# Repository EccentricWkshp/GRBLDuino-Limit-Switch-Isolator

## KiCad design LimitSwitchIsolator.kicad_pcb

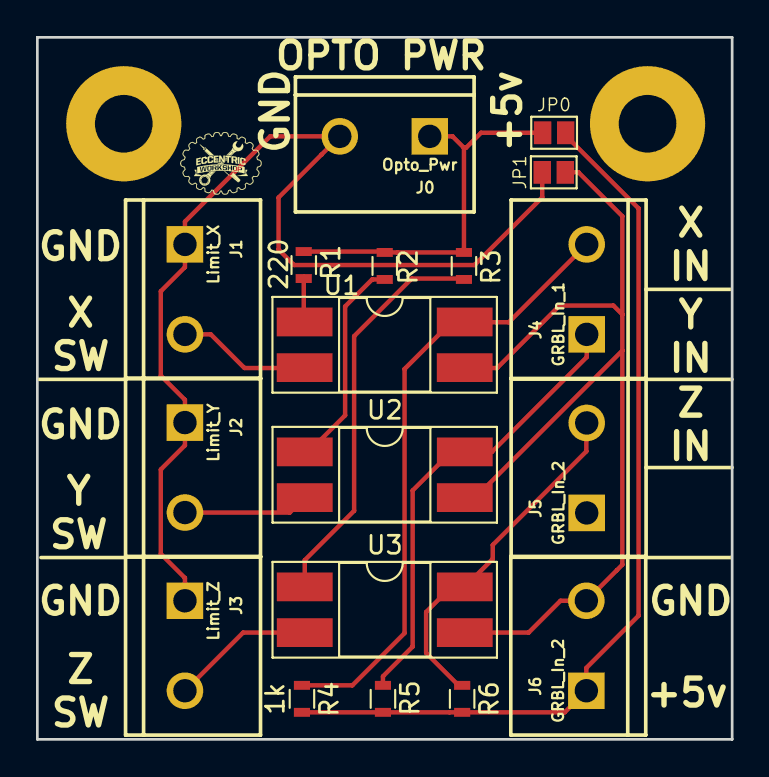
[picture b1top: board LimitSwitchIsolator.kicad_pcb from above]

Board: 2 copper layers, 38.6 x 39.0 mm, 18 parts (0 on the bottom side), 13 nets.

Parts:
J0: Opto_Pwr; SPARKFUN-CONNECTORS_SCREWTERMINAL-5MM-2
J1: Limit_X; SPARKFUN-CONNECTORS_SCREWTERMINAL-5MM-2
J2: Limit_Y; SPARKFUN-CONNECTORS_SCREWTERMINAL-5MM-2
J3: Limit_Z; SPARKFUN-CONNECTORS_SCREWTERMINAL-5MM-2
J4: GRBL_In_1; SPARKFUN-CONNECTORS_SCREWTERMINAL-5MM-2
J5, J6: GRBL_In_2; SPARKFUN-CONNECTORS_SCREWTERMINAL-5MM-2
JP0: PWR_Select; GS2
JP1: GND_Select; GS2
R1, R2, R3: 220; R_0603
R4, R5, R6: 1k; R_0603
U1, U2, U3: LTV-817; DIP-4_W8.89mm_SMDSocket_LongPads

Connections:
unnamed: J0.1, JP0.1, R1.2, R2.2, R3.2
unnamed: J0.2, J1.1, J2.1, J3.1, JP1.1
unnamed: J1.2, U1.2
unnamed: J2.2, U2.2
unnamed: J3.2, U3.2
unnamed: J4.1, R5.1, U2.4
unnamed: J4.2, R4.1, U1.4
unnamed: J5.2, R6.1, U3.4
unnamed: J6.1, JP0.2, R4.2, R5.2, R6.2
unnamed: J6.2, JP1.2, U1.3, U2.3, U3.3
unnamed: R1.1, U1.1
unnamed: R2.1, U2.1
unnamed: R3.1, U3.1
